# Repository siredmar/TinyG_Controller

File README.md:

View this project on [CADLAB.io](https://cadlab.io/project/23649). 

# TinyG_Controller

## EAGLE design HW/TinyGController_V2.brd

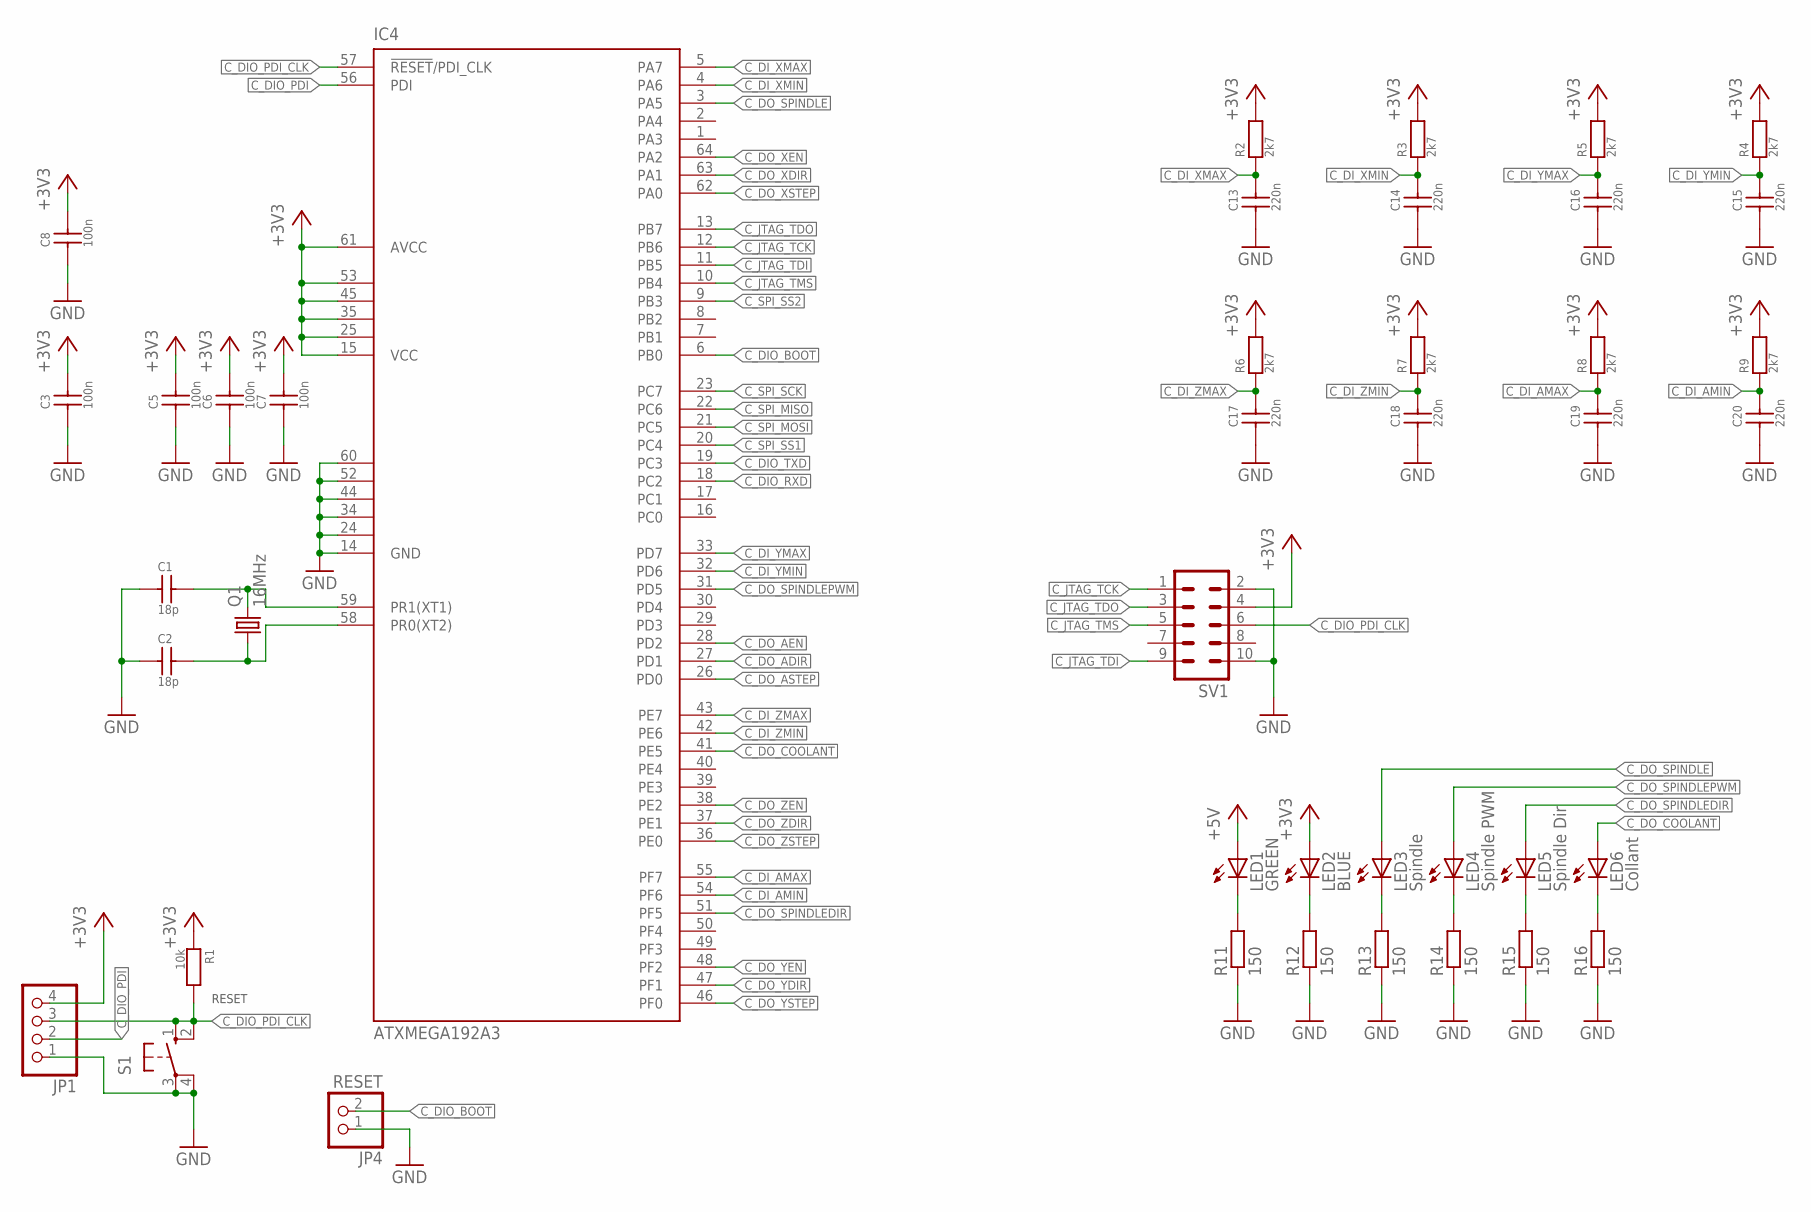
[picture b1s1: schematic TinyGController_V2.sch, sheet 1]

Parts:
C1, C2: 18p; C0603
C3, C5, C6, C7, C8: 100n; C0603
C13, C14, C15, C16, C17, C18, C19, C20: 220n; C0805
IC4: ATXMEGA192A3; TQFP64-0.8MM
JP1: PINHD-1X4; 1X04
JP4: RESET; 1X02
LED1: GREEN; CHIPLED_0805
LED2: BLUE; CHIPLED_0805
LED3: Spindle; CHIPLED_0805
LED4: Spindle PWM; CHIPLED_0805
LED5: Spindle Dir; CHIPLED_0805
LED6: Collant; CHIPLED_0805
Q1: 16MHz; HC49/USSM
R1: 10k; R0603
R2, R3, R4, R5, R6, R7, R8, R9: 2k7; R0603
R11, R12, R13, R14, R15, R16: 150; R0603
S1: 10-XX; B3F-10XX
SV1: ML10

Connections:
+3V3: C3.2, C5.2, C6.2, C7.2, C8.2, IC4.15 (VCC), IC4.25 (VCC1), IC4.35 (VCC2), IC4.45 (VCC3), IC4.53 (VCC4), IC4.61 (AVCC), JP1.4, LED2.A, R1.1, R2.2, R3.2, R4.2, R5.2, R6.2, R7.2, R8.2, R9.2, SV1.4; also elsewhere on the board
+5V: LED1.A; also elsewhere on the board
C_DIO_BOOT: IC4.6 (PB0), JP4.2
C_DIO_PDI: IC4.56 (PDI), JP1.2
C_DIO_PDI_CLK: IC4.57 (!RESET!/PDI_CLK), JP1.3, R1.2, S1.1 (S), S1.2 (S1), SV1.6
C_DIO_RXD: IC4.18 (PC2); also elsewhere on the board
C_DIO_TXD: IC4.19 (PC3); also elsewhere on the board
C_DI_AMAX: C19.2, IC4.55 (PF7), R8.1; also elsewhere on the board
C_DI_AMIN: C20.2, IC4.54 (PF6), R9.1; also elsewhere on the board
C_DI_XMAX: C13.2, IC4.5 (PA7), R2.1; also elsewhere on the board
C_DI_XMIN: C14.2, IC4.4 (PA6), R3.1; also elsewhere on the board
C_DI_YMAX: C16.2, IC4.33 (PD7), R5.1; also elsewhere on the board
C_DI_YMIN: C15.2, IC4.32 (PD6), R4.1; also elsewhere on the board
C_DI_ZMAX: C17.2, IC4.43 (PE7), R6.1; also elsewhere on the board
C_DI_ZMIN: C18.2, IC4.42 (PE6), R7.1; also elsewhere on the board
C_DO_!AEN: IC4.28 (PD2); also elsewhere on the board
C_DO_!XEN: IC4.64 (PA2); also elsewhere on the board
C_DO_!YEN: IC4.48 (PF2); also elsewhere on the board
C_DO_!ZEN: IC4.38 (PE2); also elsewhere on the board
C_DO_ADIR: IC4.27 (PD1); also elsewhere on the board
C_DO_ASTEP: IC4.26 (PD0); also elsewhere on the board
C_DO_COOLANT: IC4.41 (PE5), LED6.A; also elsewhere on the board
C_DO_SPINDLE: IC4.3 (PA5), LED3.A; also elsewhere on the board
C_DO_SPINDLEDIR: IC4.51 (PF5), LED5.A; also elsewhere on the board
C_DO_SPINDLEPWM: IC4.31 (PD5), LED4.A; also elsewhere on the board
C_DO_XDIR: IC4.63 (PA1); also elsewhere on the board
C_DO_XSTEP: IC4.62 (PA0); also elsewhere on the board
C_DO_YDIR: IC4.47 (PF1); also elsewhere on the board
C_DO_YSTEP: IC4.46 (PF0); also elsewhere on the board
C_DO_ZDIR: IC4.37 (PE1); also elsewhere on the board
C_DO_ZSTEP: IC4.36 (PE0); also elsewhere on the board
C_JTAG_TCK: IC4.12 (PB6), SV1.1
C_JTAG_TDI: IC4.11 (PB5), SV1.9
C_JTAG_TDO: IC4.13 (PB7), SV1.3
C_JTAG_TMS: IC4.10 (PB4), SV1.5
C_SPI_!SS1: IC4.20 (PC4); also elsewhere on the board
C_SPI_!SS2: IC4.9 (PB3); also elsewhere on the board
C_SPI_MISO: IC4.22 (PC6); also elsewhere on the board
C_SPI_MOSI: IC4.21 (PC5); also elsewhere on the board
C_SPI_SCK: IC4.23 (PC7); also elsewhere on the board
GND: C1.1, C2.1, C3.1, C5.1, C6.1, C7.1, C8.1, C13.1, C14.1, C15.1, C16.1, C17.1, C18.1, C19.1, C20.1, IC4.14 (GND), IC4.24 (GND1), IC4.34 (GND2), IC4.44 (GND3), IC4.52 (GND4), IC4.60 (GND5), JP1.1, JP4.1, R11.1, R12.1, R13.1, R14.1, R15.1, R16.1, S1.3, S1.4 (P1), SV1.2, SV1.10; also elsewhere on the board
unnamed: C1.2, IC4.59 (PR1(XT1)), Q1.2
unnamed: C2.2, IC4.58 (PR0(XT2)), Q1.1
unnamed: LED1.C, R11.2
unnamed: LED2.C, R12.2
unnamed: LED3.C, R13.2
unnamed: LED4.C, R14.2
unnamed: LED5.C, R15.2
unnamed: LED6.C, R16.2

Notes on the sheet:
RESET

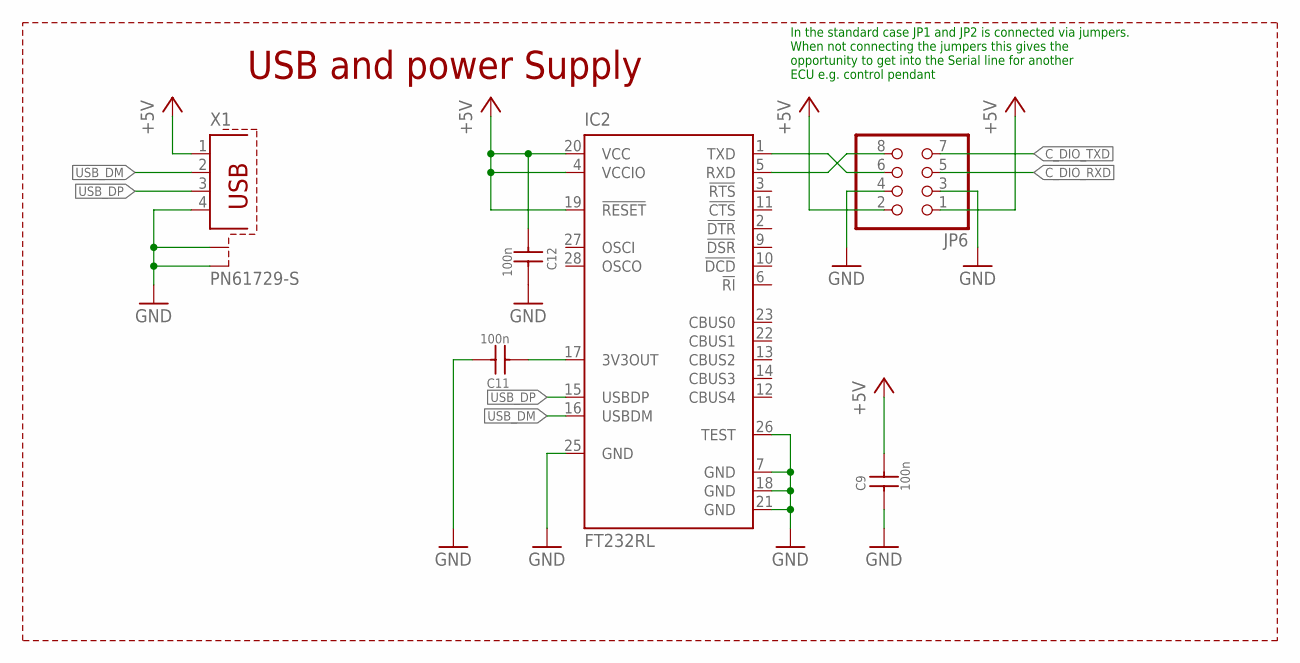
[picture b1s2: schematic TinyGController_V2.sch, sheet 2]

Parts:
C9, C11, C12: 100n; C0603
IC2: FT232RL; SSOP28
JP6: PINHD-2X4; 2X04
X1: PN61729-S

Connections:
+5V: C9.2, C12.1, IC2.4 (VCCIO), IC2.19 (!RESET), IC2.20 (VCC), JP6.1, JP6.2, X1.1; also elsewhere on the board
C_DIO_RXD: JP6.5; also elsewhere on the board
C_DIO_TXD: JP6.7; also elsewhere on the board
FTDI_3V3OUT: C11.1, IC2.17 (3V3OUT)
GND: C9.1, C11.2, C12.2, IC2.7 (GND), IC2.18 (GND), IC2.21 (GND), IC2.25 (GND), IC2.26 (TEST), JP6.3, JP6.4, X1.4, X1.S1, X1.S2; also elsewhere on the board
unnamed: IC2.1 (TXD), JP6.6
unnamed: IC2.5 (RXD), JP6.8
USB_DM: IC2.16 (USBDM), X1.2
USB_DP: IC2.15 (USBDP), X1.3

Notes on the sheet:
In the standard case JP1 and JP2 is connected via jumpers. When not connecting the jumpers this gives the opportunity to get into the Serial line for another ECU e.g. control pendant
USB and power Supply

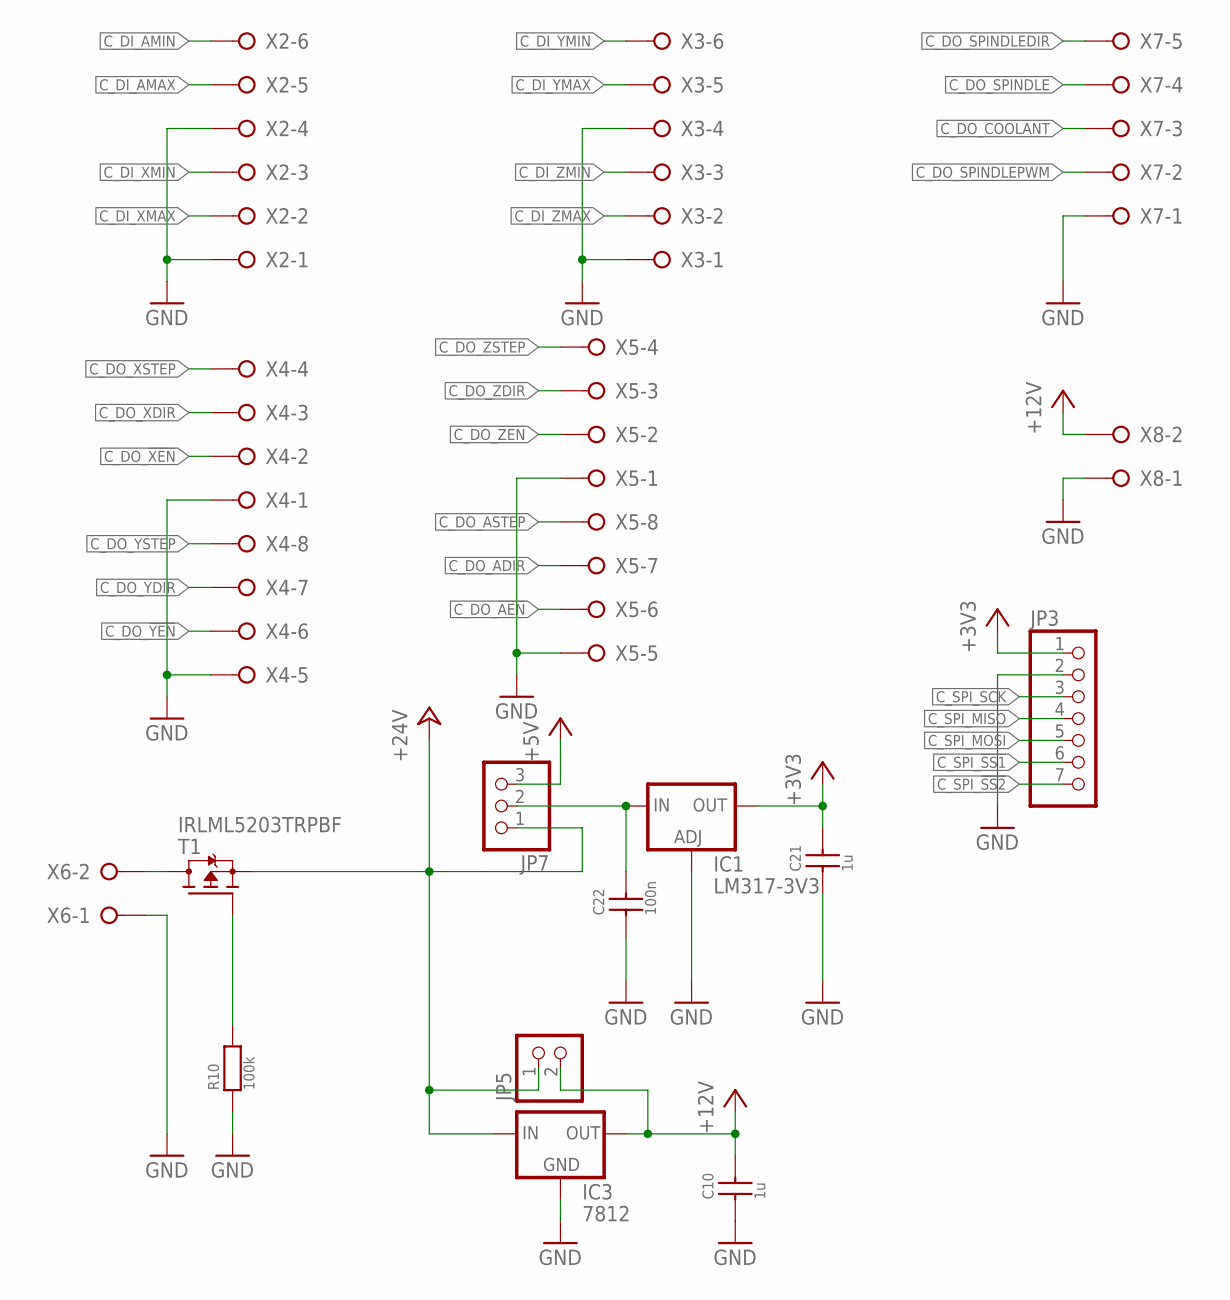
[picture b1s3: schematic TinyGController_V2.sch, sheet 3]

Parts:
C10, C21: 1u; C0805
C22: 100n; C0805
IC1: LM317-3V3; SOT223
IC3: 7812; 78XXS
JP3: PINHD-1X7; 1X07
JP5: PINHD-1X2; 1X02
JP7: PINHD-1X3; 1X03
R10: 100k; R0603
T1: IRLML5203TRPBF; SOT23
X2, X3: W237-06P; W237-6P
X4, X5: W237-08P; W237-8P
X6, X8: W237-02P; W237-132
X7: W237-05P; W237-5P

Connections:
+3V3: C21.2, IC1.4 (OUT), JP3.1; also elsewhere on the board
+5V: JP7.3; also elsewhere on the board
+12V: C10.2, IC3.OUT, JP5.2, X8.2
+24V: IC3.IN, JP5.1, JP7.1, T1.2 (S)
C_DI_AMAX: X2.5; also elsewhere on the board
C_DI_AMIN: X2.6; also elsewhere on the board
C_DI_XMAX: X2.2; also elsewhere on the board
C_DI_XMIN: X2.3; also elsewhere on the board
C_DI_YMAX: X3.5; also elsewhere on the board
C_DI_YMIN: X3.6; also elsewhere on the board
C_DI_ZMAX: X3.2; also elsewhere on the board
C_DI_ZMIN: X3.3; also elsewhere on the board
C_DO_!AEN: X5.6; also elsewhere on the board
C_DO_!XEN: X4.2; also elsewhere on the board
C_DO_!YEN: X4.6; also elsewhere on the board
C_DO_!ZEN: X5.2; also elsewhere on the board
C_DO_ADIR: X5.7; also elsewhere on the board
C_DO_ASTEP: X5.8; also elsewhere on the board
C_DO_COOLANT: X7.3; also elsewhere on the board
C_DO_SPINDLE: X7.4; also elsewhere on the board
C_DO_SPINDLEDIR: X7.5; also elsewhere on the board
C_DO_SPINDLEPWM: X7.2; also elsewhere on the board
C_DO_XDIR: X4.3; also elsewhere on the board
C_DO_XSTEP: X4.4; also elsewhere on the board
C_DO_YDIR: X4.7; also elsewhere on the board
C_DO_YSTEP: X4.8; also elsewhere on the board
C_DO_ZDIR: X5.3; also elsewhere on the board
C_DO_ZSTEP: X5.4; also elsewhere on the board
C_SPI_!SS1: JP3.6; also elsewhere on the board
C_SPI_!SS2: JP3.7; also elsewhere on the board
C_SPI_MISO: JP3.4; also elsewhere on the board
C_SPI_MOSI: JP3.5; also elsewhere on the board
C_SPI_SCK: JP3.3; also elsewhere on the board
GND: C10.1, C21.1, C22.1, IC1.1 (ADJ), IC3.GND, JP3.2, R10.1, X2.1, X2.4, X3.1, X3.4, X4.1, X4.5, X5.1, X5.5, X6.1, X7.1, X8.1; also elsewhere on the board
unnamed: R10.2, T1.1 (G)
unnamed: T1.3 (D), X6.2
unnamed: C22.2, IC1.3 (IN), JP7.2

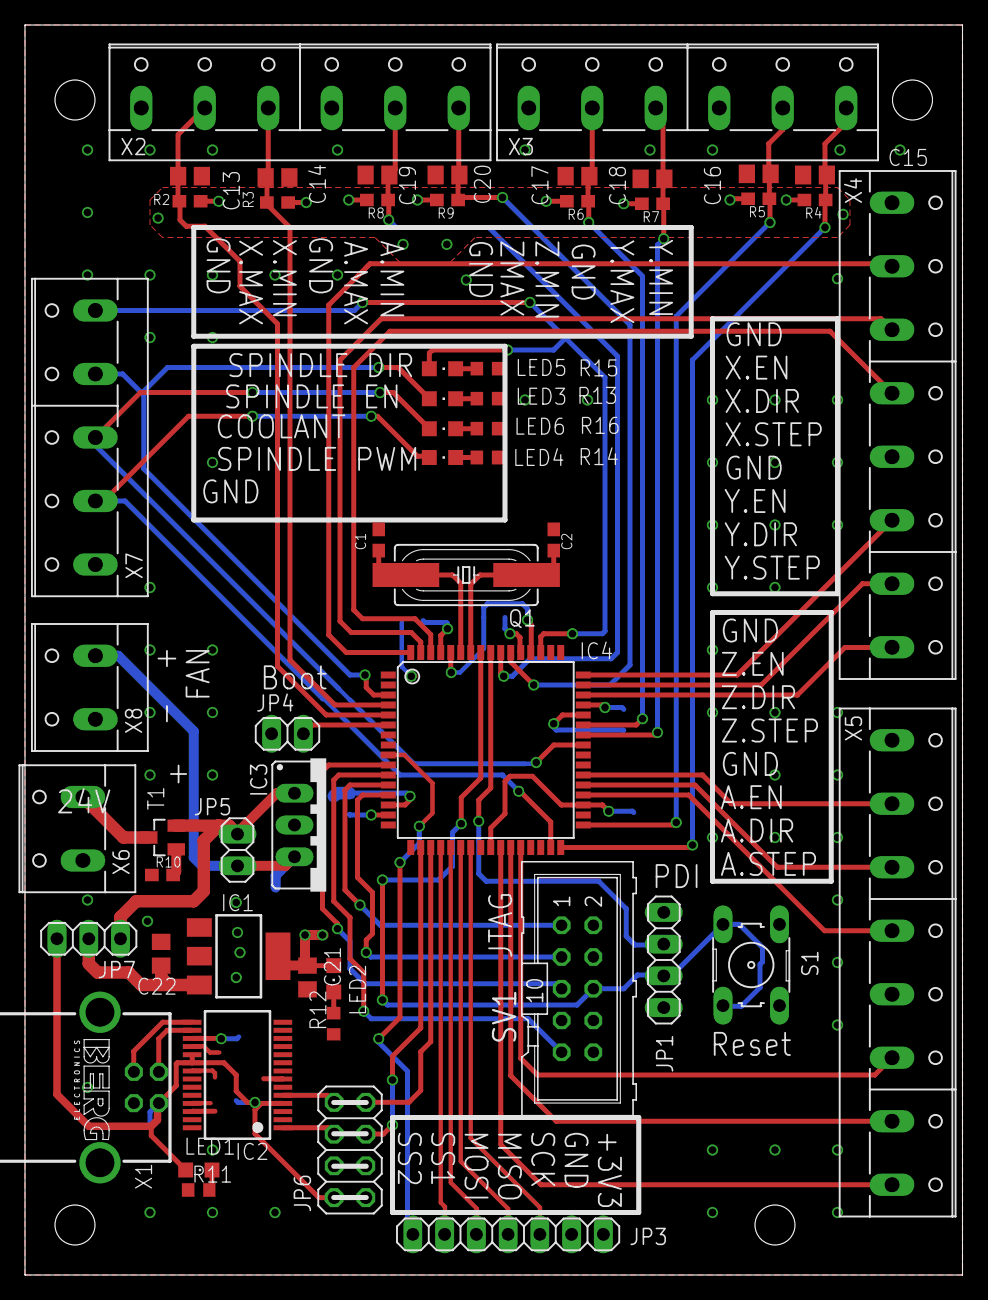
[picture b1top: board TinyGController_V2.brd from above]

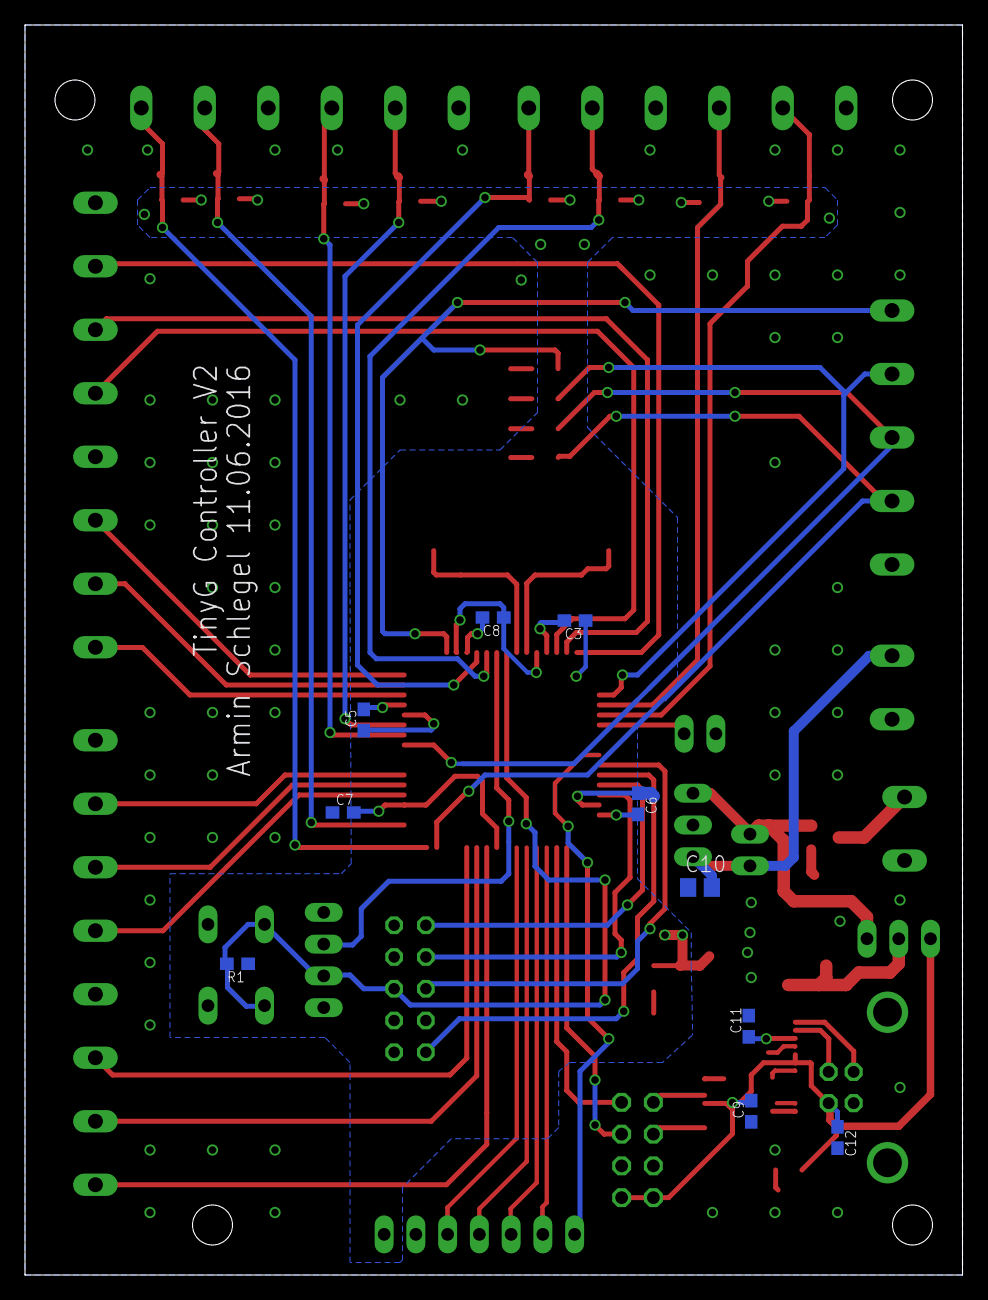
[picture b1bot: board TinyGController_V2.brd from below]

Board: 2 copper layers, 75.0 x 100.0 mm, 65 parts (10 on the bottom side), 59 nets.

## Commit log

2016-03-31 First version of TinyG Controller
2016-06-16 Added final V1 and V2 in development
2016-06-16 Added Pictures of Version 1
2020-12-15 Backlink to CADLAB.io has been added.
